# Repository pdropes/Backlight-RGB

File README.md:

# Backlight-RGB
LED lighting control

Small circuit to control an LED strip by computer

- Attiny25 programed in Bascom AVR
- PC interface in Visual Basic 6 on Windows 7 32bits

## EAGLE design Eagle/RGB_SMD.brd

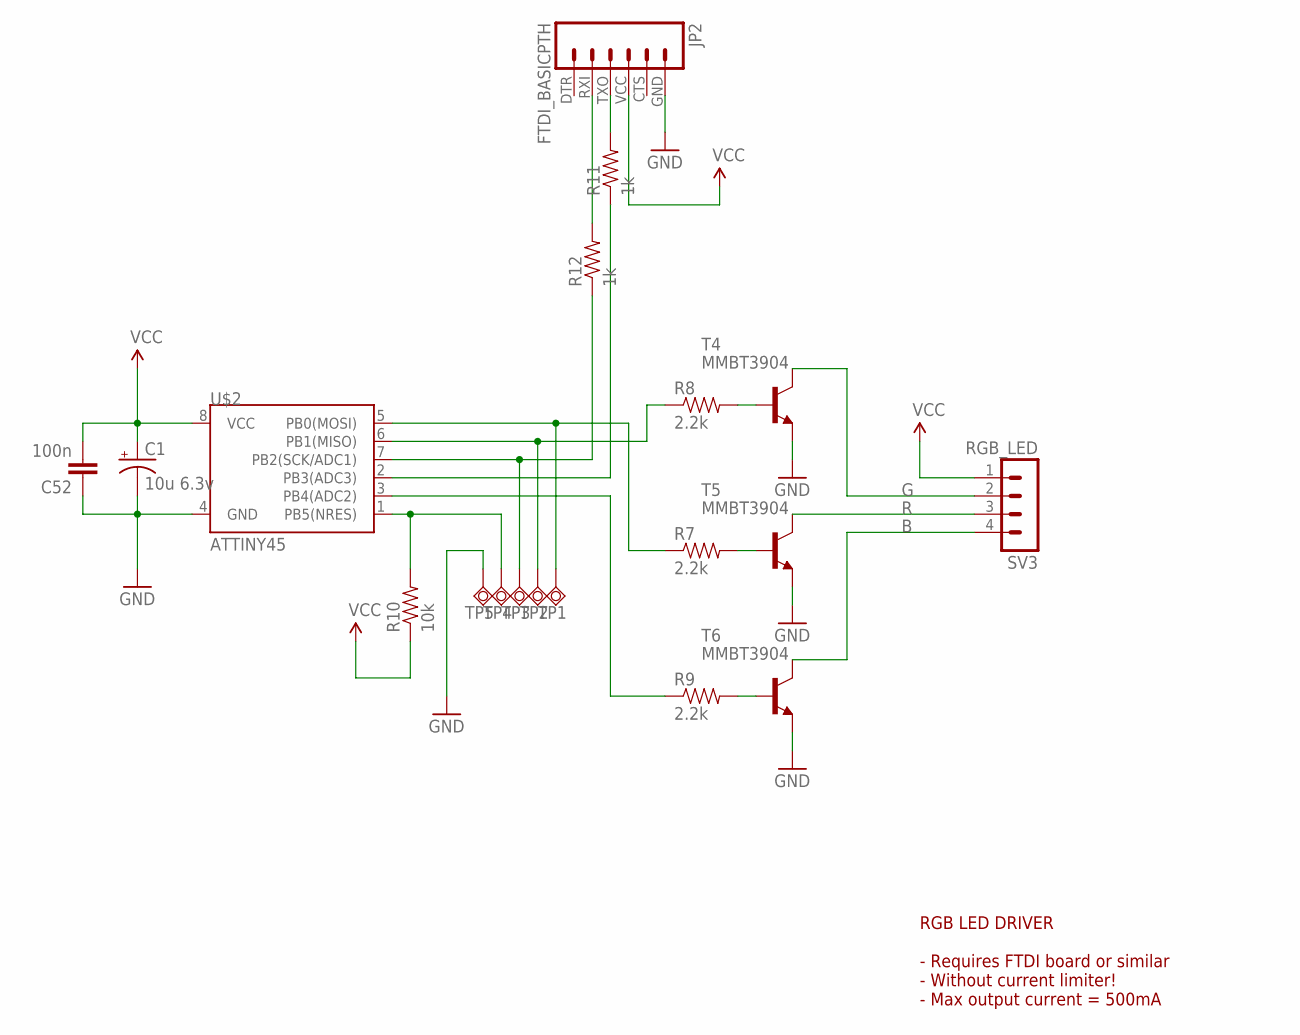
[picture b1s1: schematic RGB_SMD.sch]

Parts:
C1: 10u 6.3v; EIA3216
C52: 100n; 0805
JP2: FTDI_BASICPTH; FTDI_BASIC
R7, R8, R9: 2.2k; 0805
R10: 10k; 0805
R11, R12: 1k; 0805
SV3: RGB_LED; MA04-1
T4, T5, T6: MMBT3904; SOT23-BEC
TP1, TP2, TP3, TP4, TP5: TPSQTP16SQ; TP16SQ
U$2: ATTINY45; SO08-EIAJ

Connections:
B: SV3.4, T6.C
G: SV3.2, T4.C
GND: C1.C (-), C52.1, JP2.GND (6), T4.E, T5.E, T6.E, TP5.TP, U$2.4 (GND)
unnamed: JP2.TXO (3), R11.2
unnamed: JP2.RXI (2), R12.2
unnamed: R10.2, TP4.TP, U$2.1 (PB5(NRES))
unnamed: R11.1, U$2.2 (PB3(ADC3))
unnamed: R12.1, TP3.TP, U$2.7 (PB2(SCK/ADC1))
unnamed: R7.1, TP1.TP, U$2.5 (PB0(MOSI))
unnamed: R8.1, TP2.TP, U$2.6 (PB1(MISO))
unnamed: R9.1, U$2.3 (PB4(ADC2))
unnamed: R9.2, T6.B
unnamed: R7.2, T5.B
unnamed: R8.2, T4.B
R: SV3.3, T5.C
VCC: C1.A (+), C52.2, JP2.VCC (4), R10.1, SV3.1, U$2.8 (VCC)

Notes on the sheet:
RGB LED DRIVER - Requires FTDI board or similar - Without current limiter! - Max output current = 500mA

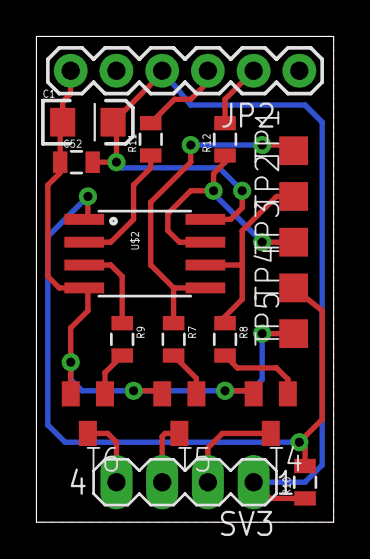
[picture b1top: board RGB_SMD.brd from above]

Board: 2 copper layers, 16.5 x 27.0 mm, 19 parts (0 on the bottom side), 16 nets.

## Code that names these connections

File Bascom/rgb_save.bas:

'Pinout ATtiny25:
'1- PB5 (PCINT5 / Reset / ADC0 / DW)
'2- PB3 (PCINT3/XTAL1/CLKI/OC1B/ADC3)
'3- PB4 (PCINT4/XTAL2/CLKO/_OC1B/ADC2)
'4- GND
'5- PB0 (MOSI/DI/SDA/AIN0/OC0A/OC1A/AREF/PCINT0)
'6- PB1 (MISO/DO/AIN1/OC0B/OC1A/PCINT1)
'7- PB2 (SCK/USCK/SCL/ADC1/T0/INT0/PCINT2)
'8- VCC

'             PCINT5/RESET/ADC0/DW PB5 [1 U 8] VCC
' PCINT3/XTAL1/CLKI/OC1B/ADC3 PB3 [2    7] PB2 SCK/USCK/SCL/ADC1/T0/INT0/PCINT2
'PCINT4/XTAL2/CLKO/OC1B/ADC2 PB4 [3    6] PB1 MISO/DO/AIN1/OC0B/OC1A/PCINT1
'                                                   GND [4    5] PB0 MOSI/DI/SDA/AIN0/OC0A/OC1A/AREF/PCINT0
'
'
$regfile = "attiny25.dat"
$crystal = 16000000
'$hwstack = 64
'$swstack = 32
'$framesize = 32

'--------------------------------------Software UART-------------------------------------
Open "comb.3:4800,8,n,1" For Input As #1

Const Red = 0
Const Green = 1
Const Blue = 4

Dim R , G , B As Byte
Dim Value As Byte
Dim Ident As Byte
Dim Ee_r , Ee_g , Ee_b As Eram Byte

'---------------------------------------DISPLAY-------------------------------------------
Main:
    Config Portb.red = Output
    Config Portb.green = Output
    Config Portb.blue = Output

'Configure counter/timer0 for fast PWM on PB0 and PB1
 'COM0A1 COM0A0 COM0B1 COM0B0   WGM01 WGM00
    Tccr0a = &B11110011                                     '64khz
 ' FOC0A FOC0B   WGM02 CS02 CS01 CS00
    Tccr0b = &B00000001                                     '64khz
'Configure counter/timer1 for fast PWM on PB4
' TSM PWM1B COM1B1 COM1B0 FOC1B FOC1A PSR1 PSR0
    Gtccr = &B01110000
'CTC1 PWM1A COM1A1 COM1A0 CS13 CS12 CS11 CS10
    Tccr1 = &B00110100                                      '32khz

'---------------------------PLL AS CLOCK SOURCE for 16MHz---------------------------
    Pllcsr.plle = 1
    While Pllcsr.plock = 0
    Wend
    Pllcsr.pcke = 1
    !Ldi R24 , 85                                           '16MHZ
    !Out Osccal , R24
'----------------------------------SHOW PWM VALUES-----------------------------------
    R = Ee_r
    G = Ee_g
    B = Ee_b

    Ocr0a = R
    Ocr0b = G
    Ocr1b = B

    'espera que a comunicação USB estabilize
    Wait 3
    Enable Interrupts

    'Saída 62500Hz exactos para baud correto
    'Ocr0a = 127
    'Ocr0b = 127
    'Ocr1b = 127
    'Do
    'Loop

    'O valor é recebido 2 vezes, 1ª identificação,  2ª valor a exibir/gravar
    Do
        Value = Waitkey(#1)
        Ident = Value And 3
        If Value < 4 Then
            Value = Waitkey(#1)
            Select Case Ident
                Case 0 : R = 255 - Value
                Case 1 : G = 255 - Value
                Case 2 : B = 255 - Value
                Case 3 :
                    Ee_r = R
                    Ee_g = G
                    Ee_b = B
                     'pequeno flash
                    Ocr0a = 0
                    Ocr0b = 0
                    Ocr1b = 0
                    Waitms 10
                    Ocr0a = R
                    Ocr0b = G
                    Ocr1b = B
            End Select
        End If
        Ocr0a = R
        Ocr0b = G
        Ocr1b = B
    Loop

    End

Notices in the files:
parts and their libraries:
SparkFun: Licensing: CC v3.0 Share-Alike You are welcome to use this library for commercial purposes.
